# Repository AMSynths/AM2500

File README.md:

# AM2500 DOCUMENTATION REPO

This GitHub repository contains the documentation about the AMSynths 2500 analog synthesizer that is a replica of the ARP 2500 synthesizer from 1970.

There is documentation and open source for each AMSynths module:
* Short form Project Notes
* Eagle CAD schematics and board layouts
* Configuration and setup instructions
* 5U Panel CAD files
* Photographs of the completed modules

The AMSynths website at https://amsynths.co.uk/home/my-synths/2500-rack/ contains more detail on the build status and outcomes and has links to the audio and video demos.

If you need the original schematics go to https://guitarfool.com/ARP2500.html or purchase them from Music Parts at https://www.musicparts.com/products.asp?Company=Arp. I will not be posting the original schematics here.

The AMSynths hardware designs (PCB layouts and schematics,documentation, panel CAD) are licensed as open source under the GNU General Purpose License V3.0.

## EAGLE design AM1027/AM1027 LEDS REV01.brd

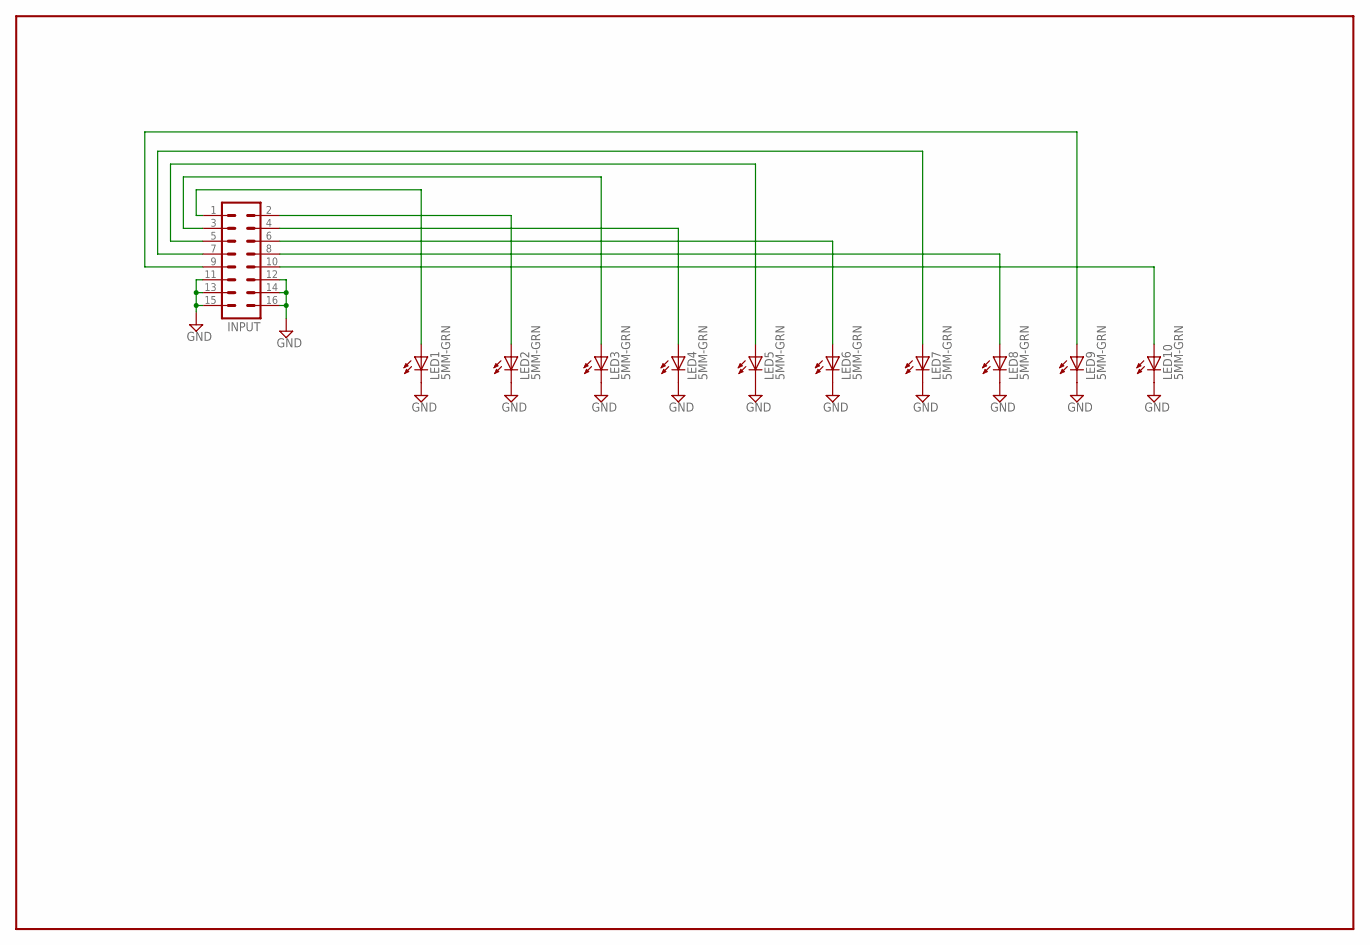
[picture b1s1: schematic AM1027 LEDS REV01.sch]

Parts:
INPUT: MA08-2-AM
LED1, LED2, LED3, LED4, LED5, LED6, LED7, LED8, LED9, LED10: 5MM-GRN; LED3MM-AMS

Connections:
GND: INPUT.11, INPUT.12, INPUT.13, INPUT.14, INPUT.15, INPUT.16, LED1.C, LED2.C, LED3.C, LED4.C, LED5.C, LED6.C, LED7.C, LED8.C, LED9.C, LED10.C
unnamed: INPUT.2, LED2.A
unnamed: INPUT.1, LED1.A
unnamed: INPUT.3, LED3.A
unnamed: INPUT.4, LED4.A
unnamed: INPUT.5, LED5.A
unnamed: INPUT.6, LED6.A
unnamed: INPUT.7, LED7.A
unnamed: INPUT.8, LED8.A
unnamed: INPUT.9, LED9.A
unnamed: INPUT.10, LED10.A

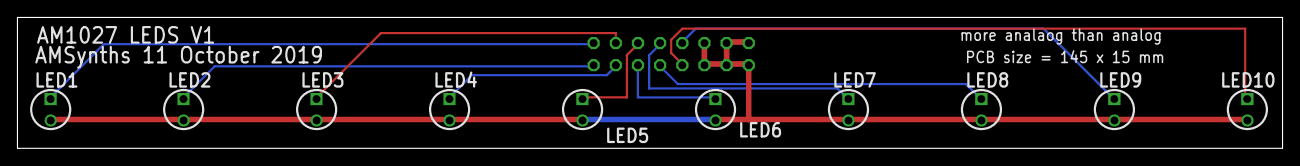
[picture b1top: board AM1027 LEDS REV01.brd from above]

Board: 2 copper layers, 145.0 x 15.0 mm, 11 parts (1 on the bottom side), 11 nets.

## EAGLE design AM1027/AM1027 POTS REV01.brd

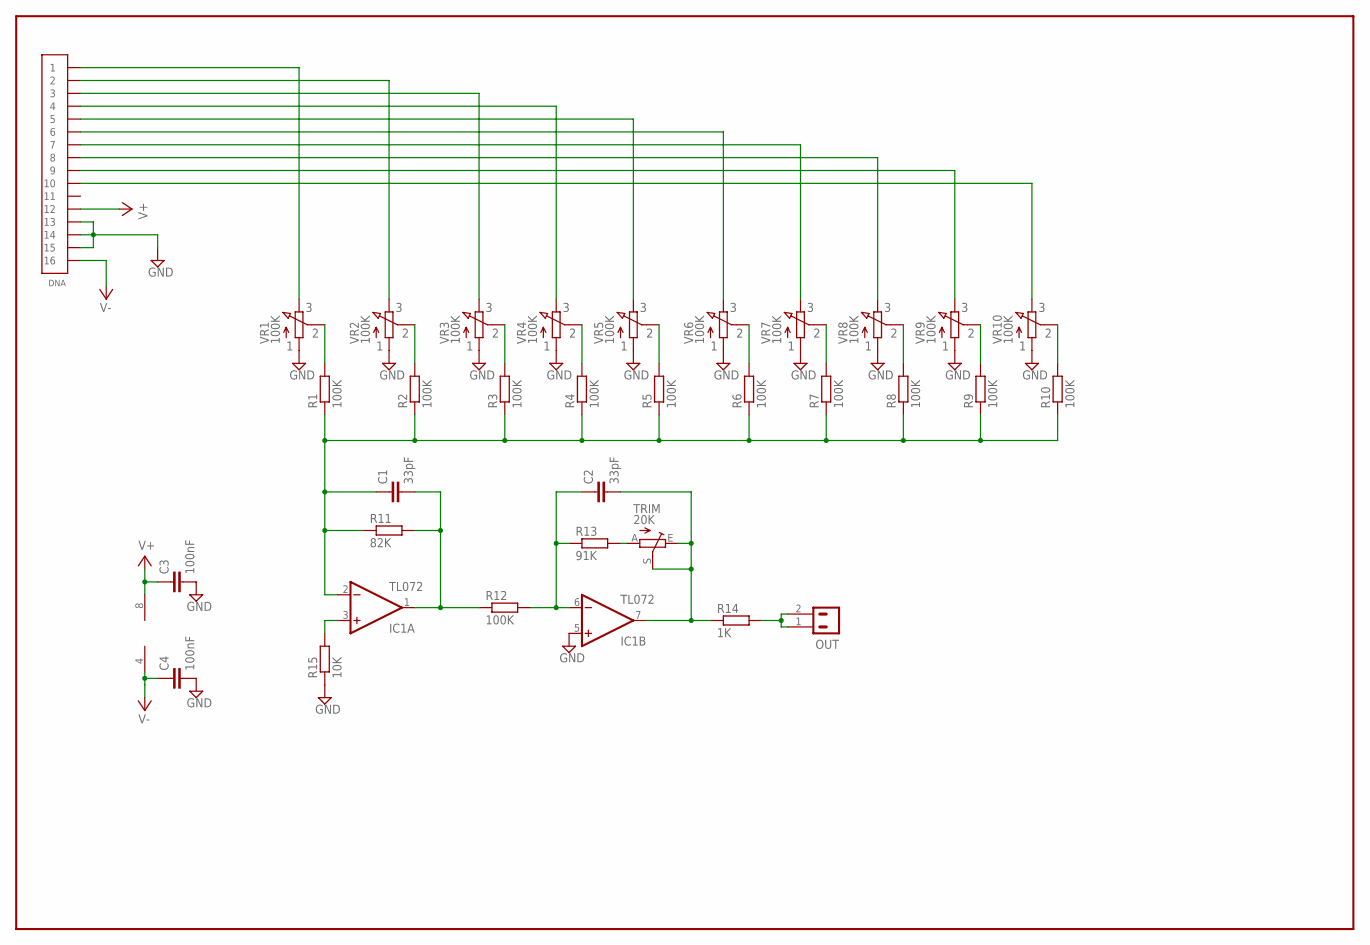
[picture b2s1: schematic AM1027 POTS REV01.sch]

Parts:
C1, C2: 33pF; C050-025X075AM
C3, C4: 100nF; C050-025X075AM
DNA: AMPWR16PIN; AMPWR16
IC1: TL072; DIL08AM
OUT: MA02-AM
R1, R2, R3, R4, R5, R6, R7, R8, R9, R10, R12: 100K; 0207/10/AM
R11: 82K; 0207/10/AM
R13: 91K; 0207/10/AM
R14: 1K; 0207/10/AM
R15: 10K; 0207/10/AM
TRIM: 20K; S64W-AM
VR1, VR2, VR3, VR4, VR5, VR6, VR7, VR8, VR9, VR10: 100K; SPECTROL148

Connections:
GND: C3.P$4 (2), C4.P$4 (2), DNA.13, DNA.14, DNA.15, IC1.5 (+IN), R15.P$1 (1), VR1.P$1 (A), VR2.P$1 (A), VR3.P$1 (A), VR4.P$1 (A), VR5.P$1 (A), VR6.P$1 (A), VR7.P$1 (A), VR8.P$1 (A), VR9.P$1 (A), VR10.P$1 (A)
unnamed: R1.P$2 (2), VR1.P$2 (S)
unnamed: R2.P$2 (2), VR2.P$2 (S)
unnamed: R3.P$2 (2), VR3.P$2 (S)
unnamed: R4.P$2 (2), VR4.P$2 (S)
unnamed: R5.P$2 (2), VR5.P$2 (S)
unnamed: R6.P$2 (2), VR6.P$2 (S)
unnamed: R7.P$2 (2), VR7.P$2 (S)
unnamed: R8.P$2 (2), VR8.P$2 (S)
unnamed: R9.P$2 (2), VR9.P$2 (S)
unnamed: R10.P$2 (2), VR10.P$2 (S)
unnamed: DNA.1, VR1.P$3 (E)
unnamed: DNA.2, VR2.P$3 (E)
unnamed: DNA.3, VR3.P$3 (E)
unnamed: DNA.4, VR4.P$3 (E)
unnamed: DNA.5, VR5.P$3 (E)
unnamed: DNA.6, VR6.P$3 (E)
unnamed: DNA.7, VR7.P$3 (E)
unnamed: DNA.8, VR8.P$3 (E)
unnamed: DNA.9, VR9.P$3 (E)
unnamed: DNA.10, VR10.P$3 (E)
unnamed: C1.P$3 (1), IC1.2 (-IN), R1.P$1 (1), R2.P$1 (1), R3.P$1 (1), R4.P$1 (1), R5.P$1 (1), R6.P$1 (1), R7.P$1 (1), R8.P$1 (1), R9.P$1 (1), R10.P$1 (1), R11.P$1 (1)
unnamed: C2.P$4 (2), IC1.7 (OUT), R14.P$1 (1), TRIM.E, TRIM.S
unnamed: C1.P$4 (2), IC1.1 (OUT), R11.P$2 (2), R12.P$1 (1)
unnamed: C2.P$3 (1), IC1.6 (-IN), R12.P$2 (2), R13.P$1 (1)
unnamed: IC1.3 (+IN), R15.P$2 (2)
unnamed: R13.P$2 (2), TRIM.A
unnamed: OUT.1, OUT.2, R14.P$2 (2)
V+: C3.P$3 (1), DNA.12, IC1.8 (V+)
V-: C4.P$3 (1), DNA.16, IC1.4 (V-)

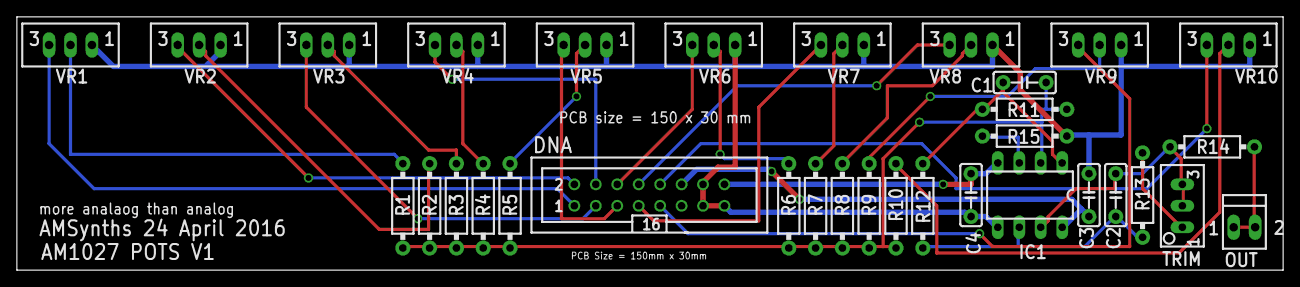
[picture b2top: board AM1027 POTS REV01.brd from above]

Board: 2 copper layers, 150.0 x 30.0 mm, 33 parts (0 on the bottom side), 30 nets.

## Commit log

2019-04-10 Create AM1006
2019-04-10 Create Hardware Design
2019-04-11 Eagle CAD files for the POTS PCB
2019-04-11 Panel CAD File for AM1047
    Open with Target V3001! software from BETA-Layout
2019-04-11 Panel CAD file for AM1006
    Open file with TARGET V3001! software from BETA-Layout
2019-04-11 Panel Readme file added
2019-04-12 Update LICENSE
2019-04-12 Create LICENSE
2019-11-11 Create AM1004 VCO
